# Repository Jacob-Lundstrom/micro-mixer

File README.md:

# micro-mixer
 Comprehensive public release repo for the Micro Mixer project

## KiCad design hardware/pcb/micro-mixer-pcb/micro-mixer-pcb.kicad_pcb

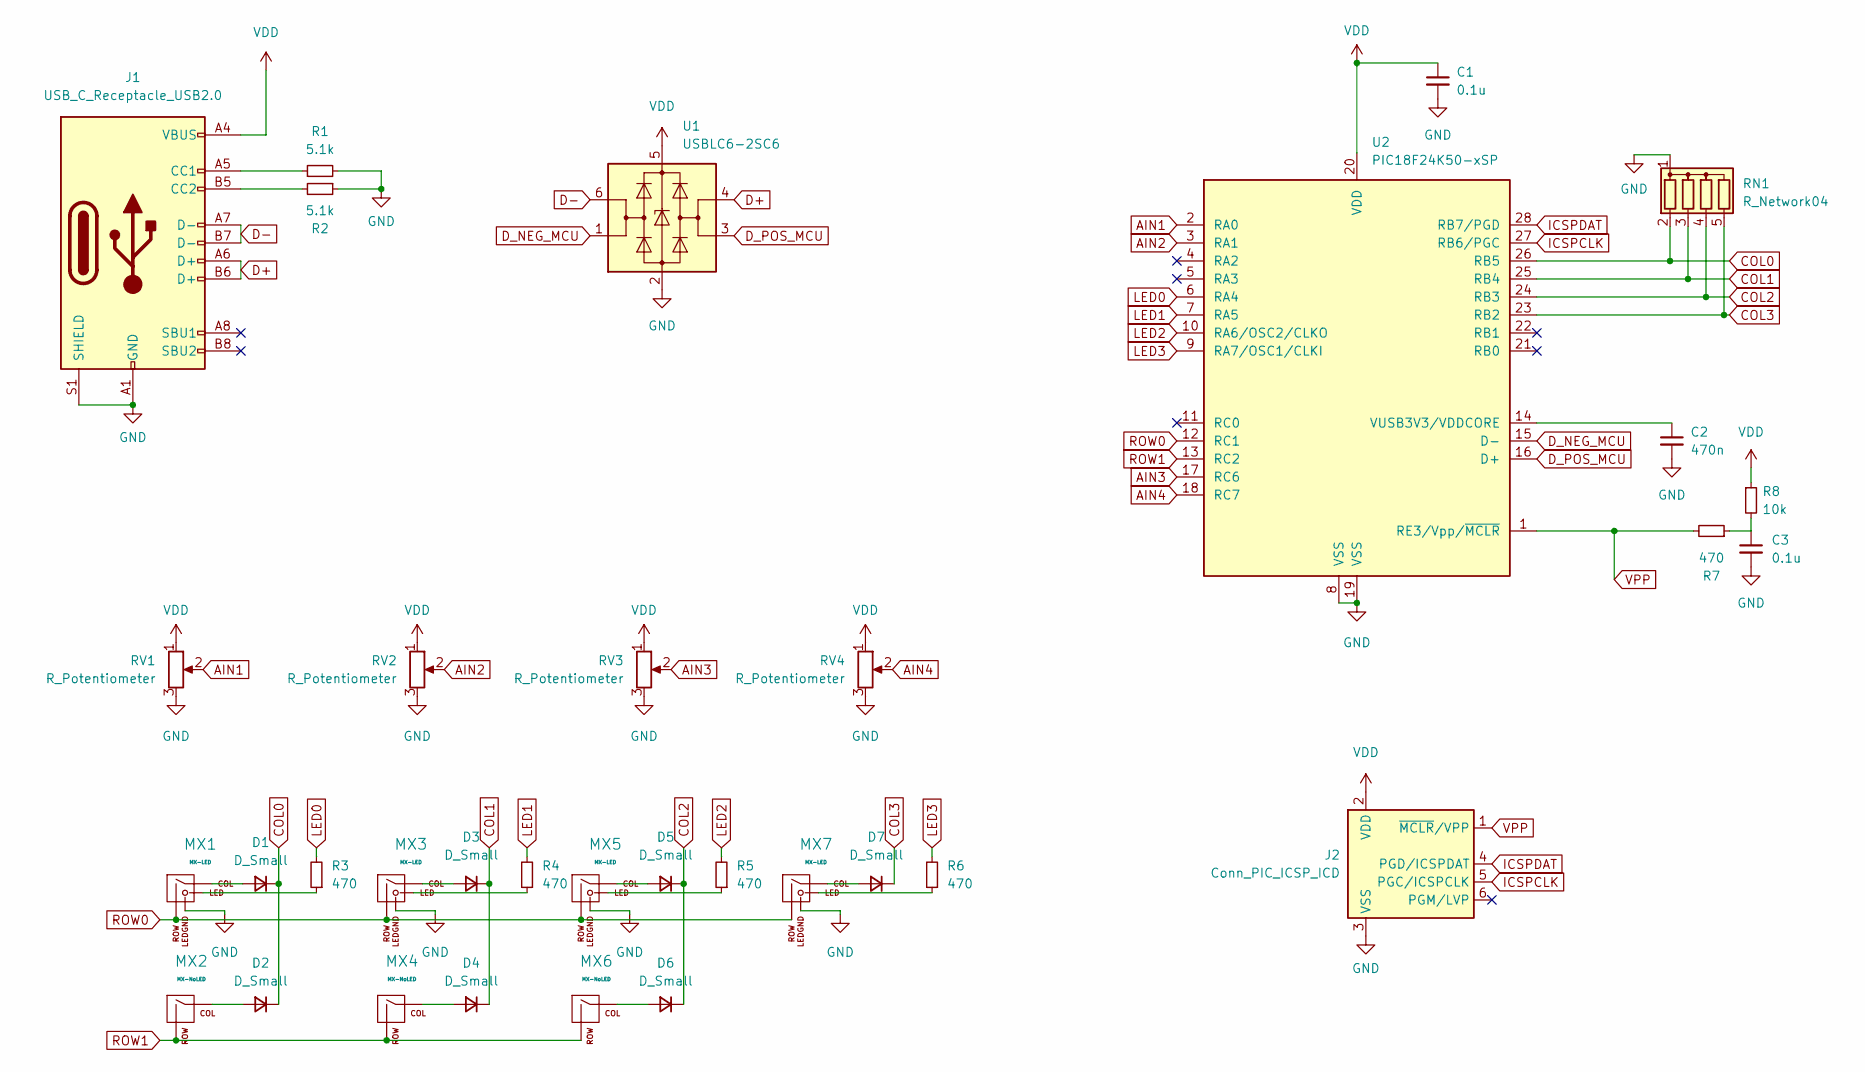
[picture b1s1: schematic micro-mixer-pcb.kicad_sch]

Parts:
C1, C3: 0.1u; C_Disc_D5.1mm_W3.2mm_P5.00mm
C2: 470n; C_Disc_D5.1mm_W3.2mm_P5.00mm
D1, D2, D3, D4, D5, D6, D7: D_Small; D_DO-34_SOD68_P7.62mm_Horizontal
J1: USB_C_Receptacle_USB2.0; USB_C_Receptacle_XKB_U262-16XN-4BVC11
J2: Conn_PIC_ICSP_ICD; PinHeader_1x06_P2.54mm_Vertical
MX1, MX3, MX5, MX7: MX-LED; MXOnly-1U
MX2, MX4, MX6: MX-NoLED; MXOnly-1U-NoLED
R1, R2: 5.1k; R_Axial_DIN0309_L9.0mm_D3.2mm_P12.70mm_Horizontal
R3, R4, R5, R6, R7: 470; R_Axial_DIN0309_L9.0mm_D3.2mm_P12.70mm_Horizontal
R8: 10k; R_Axial_DIN0309_L9.0mm_D3.2mm_P12.70mm_Horizontal
RN1: R_Network04; R_Array_SIP5
RV1, RV2, RV3, RV4: R_Potentiometer; PTB0143
U1: USBLC6-2SC6; SOT-23-6
U2: PIC18F24K50-xSP; DIP-28_W7.62mm

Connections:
AIN1: RV1.2, U2.2 (RA0)
AIN2: RV2.2, U2.3 (RA1)
AIN3: RV3.2, U2.17 (RC6)
AIN4: RV4.2, U2.18 (RC7)
COL0: D1.1 (K), D2.1 (K), RN1.2 (R1), U2.26 (RB5)
COL1: D3.1 (K), D4.1 (K), RN1.3 (R2), U2.25 (RB4)
COL2: D5.1 (K), D6.1 (K), RN1.4 (R3), U2.24 (RB3)
COL3: D7.1 (K), RN1.5 (R4), U2.23 (RB2)
D+: J1.A6 (D+), J1.B6 (D+), U1.4 (I/O2)
D-: J1.A7 (D-), J1.B7 (D-), U1.6 (I/O1)
D_NEG_MCU: U1.1 (I/O1), U2.15 (D-)
D_POS_MCU: U1.3 (I/O2), U2.16 (D+)
GND: C1.2, C2.2, C3.2, J1.A1 (GND), J1.A12 (GND), J1.B1 (GND), J1.B12 (GND), J1.S1 (SHIELD), J2.3 (VSS), MX1.4 (LEDGND), MX3.4 (LEDGND), MX5.4 (LEDGND), MX7.4 (LEDGND), R1.2, R2.1, RN1.1 (common), RV1.3, RV2.3, RV3.3, RV4.3, U1.2 (GND), U2.8 (VSS), U2.19 (VSS)
ICSPCLK: J2.5 (PGC/ICSPCLK), U2.27 (RB6/PGC)
ICSPDAT: J2.4 (PGD/ICSPDAT), U2.28 (RB7/PGD)
LED0: R3.2, U2.6 (RA4)
LED1: R4.2, U2.7 (RA5)
LED2: R5.2, U2.10 (RA6/OSC2/CLKO)
LED3: R6.2, U2.9 (RA7/OSC1/CLKI)
unnamed: C2.1, U2.14 (VUSB3V3/VDDCORE)
unnamed: C3.1, R7.1, R8.2
unnamed: D1.2 (A), MX1.1 (COL)
unnamed: D2.2 (A), MX2.1 (COL)
unnamed: D3.2 (A), MX3.1 (COL)
unnamed: D4.2 (A), MX4.1 (COL)
unnamed: D5.2 (A), MX5.1 (COL)
unnamed: D6.2 (A), MX6.1 (COL)
unnamed: D7.2 (A), MX7.1 (COL)
unnamed: J1.A5 (CC1), R1.1
unnamed: J1.B5 (CC2), R2.2
unnamed: MX1.3 (LED), R3.1
unnamed: MX3.3 (LED), R4.1
unnamed: MX5.3 (LED), R5.1
unnamed: MX7.3 (LED), R6.1
ROW0: MX1.2 (ROW), MX3.2 (ROW), MX5.2 (ROW), MX7.2 (ROW), U2.12 (RC1)
ROW1: MX2.2 (ROW), MX4.2 (ROW), MX6.2 (ROW), U2.13 (RC2)
VDD: C1.1, J1.A4 (VBUS), J1.A9 (VBUS), J1.B4 (VBUS), J1.B9 (VBUS), J2.2 (VDD), R8.1, RV1.1, RV2.1, RV3.1, RV4.1, U1.5 (VBUS), U2.20 (VDD)
VPP: J2.1 (~MCLR/VPP), R7.2, U2.1 (RE3/Vpp/~MCLR)

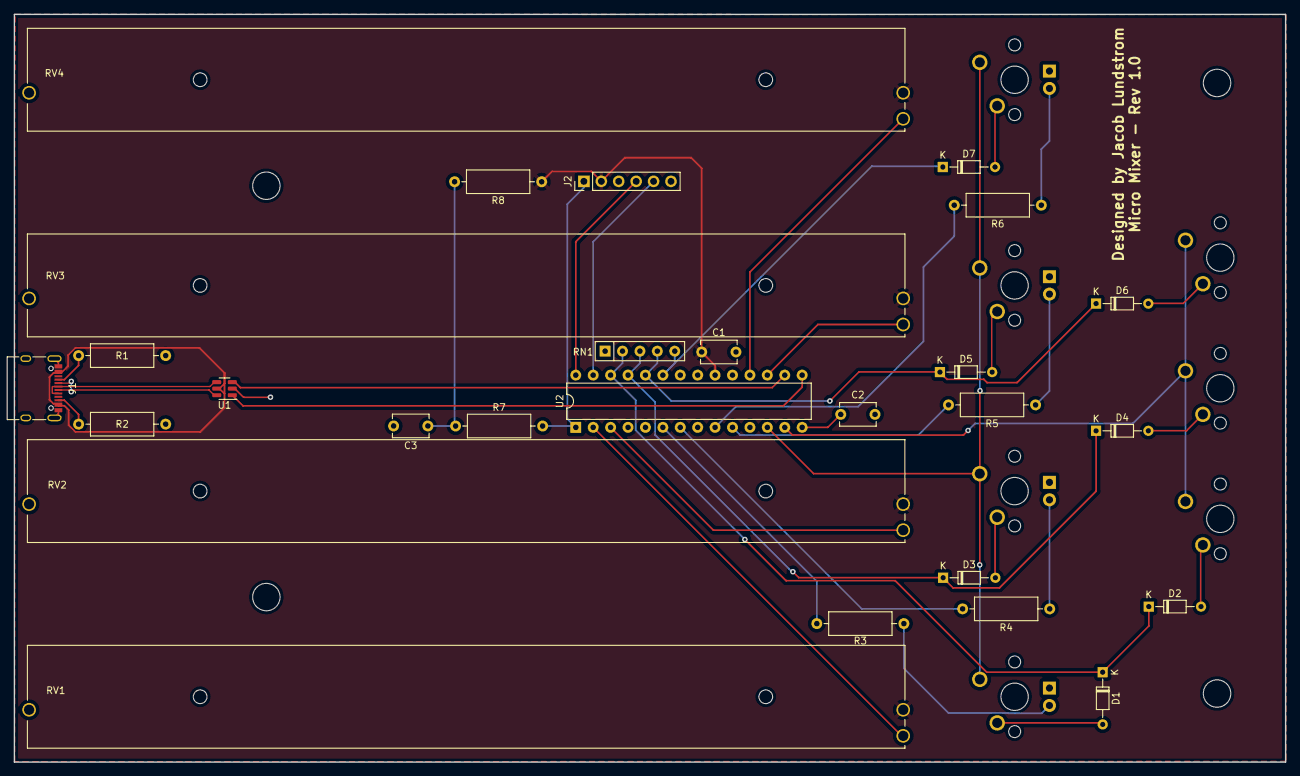
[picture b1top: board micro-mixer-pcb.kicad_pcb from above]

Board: 2 copper layers, 185.4 x 109.1 mm, 34 parts (0 on the bottom side), 38 nets.

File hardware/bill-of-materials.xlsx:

Reference | Value | Description | Digikey part No | Cost
C1 | 470n | Decoupling Cap
C2 | 470n | Decoupling Cap
D1 | D_Small | Matrix diode
D2 | D_Small | Matrix diode
D3 | D_Small | Matrix diode
D4 | D_Small | Matrix diode
D5 | D_Small | Matrix diode
D6 | D_Small | Matrix diode
D7 | D_Small | Matrix diode
J1 | USB_C_Receptacle_USB2.0 | USB type C receptacle, THT | 2073-USB4085-GF-ATR-ND | 0.94
J2 | Conn_PIC_ICSP_ICD | ICSP Port, Right angle
MX1 | MX-LED | Generic MX switch
MX2 | MX-NoLED | Generic MX switch
MX3 | MX-LED | Generic MX switch
MX4 | MX-NoLED | Generic MX switch
MX5 | MX-LED | Generic MX switch
MX6 | MX-NoLED | Generic MX switch
MX7 | MX-LED | Generic MX switch
R1 | 5.1k | USB type C orientation resistor
R2 | 5.1k | USB type C orientation resistor
RV1 | R_Potentiometer | Linear Slide Potentiometer | PTB0143-2010BPB103-ND | 6.01
RV2 | R_Potentiometer | Linear Slide Potentiometer | PTB0143-2010BPB103-ND | 6.01
RV3 | R_Potentiometer | Linear Slide Potentiometer | PTB0143-2010BPB103-ND | 6.01
RV4 | R_Potentiometer | Linear Slide Potentiometer | PTB0143-2010BPB103-ND | 6.01
U1 | USBLC6-2SC6 | USB ESD Protection | 497-5235-2-ND | 0.50700000000000001
U2 | PIC18F24K50-xSP | PIC MCU | PIC18F24K50-I/SP-ND | 3.75
 |  |  |  | 29.236999999999998 | TOTAL

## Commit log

2024-06-25 Public release of all files
